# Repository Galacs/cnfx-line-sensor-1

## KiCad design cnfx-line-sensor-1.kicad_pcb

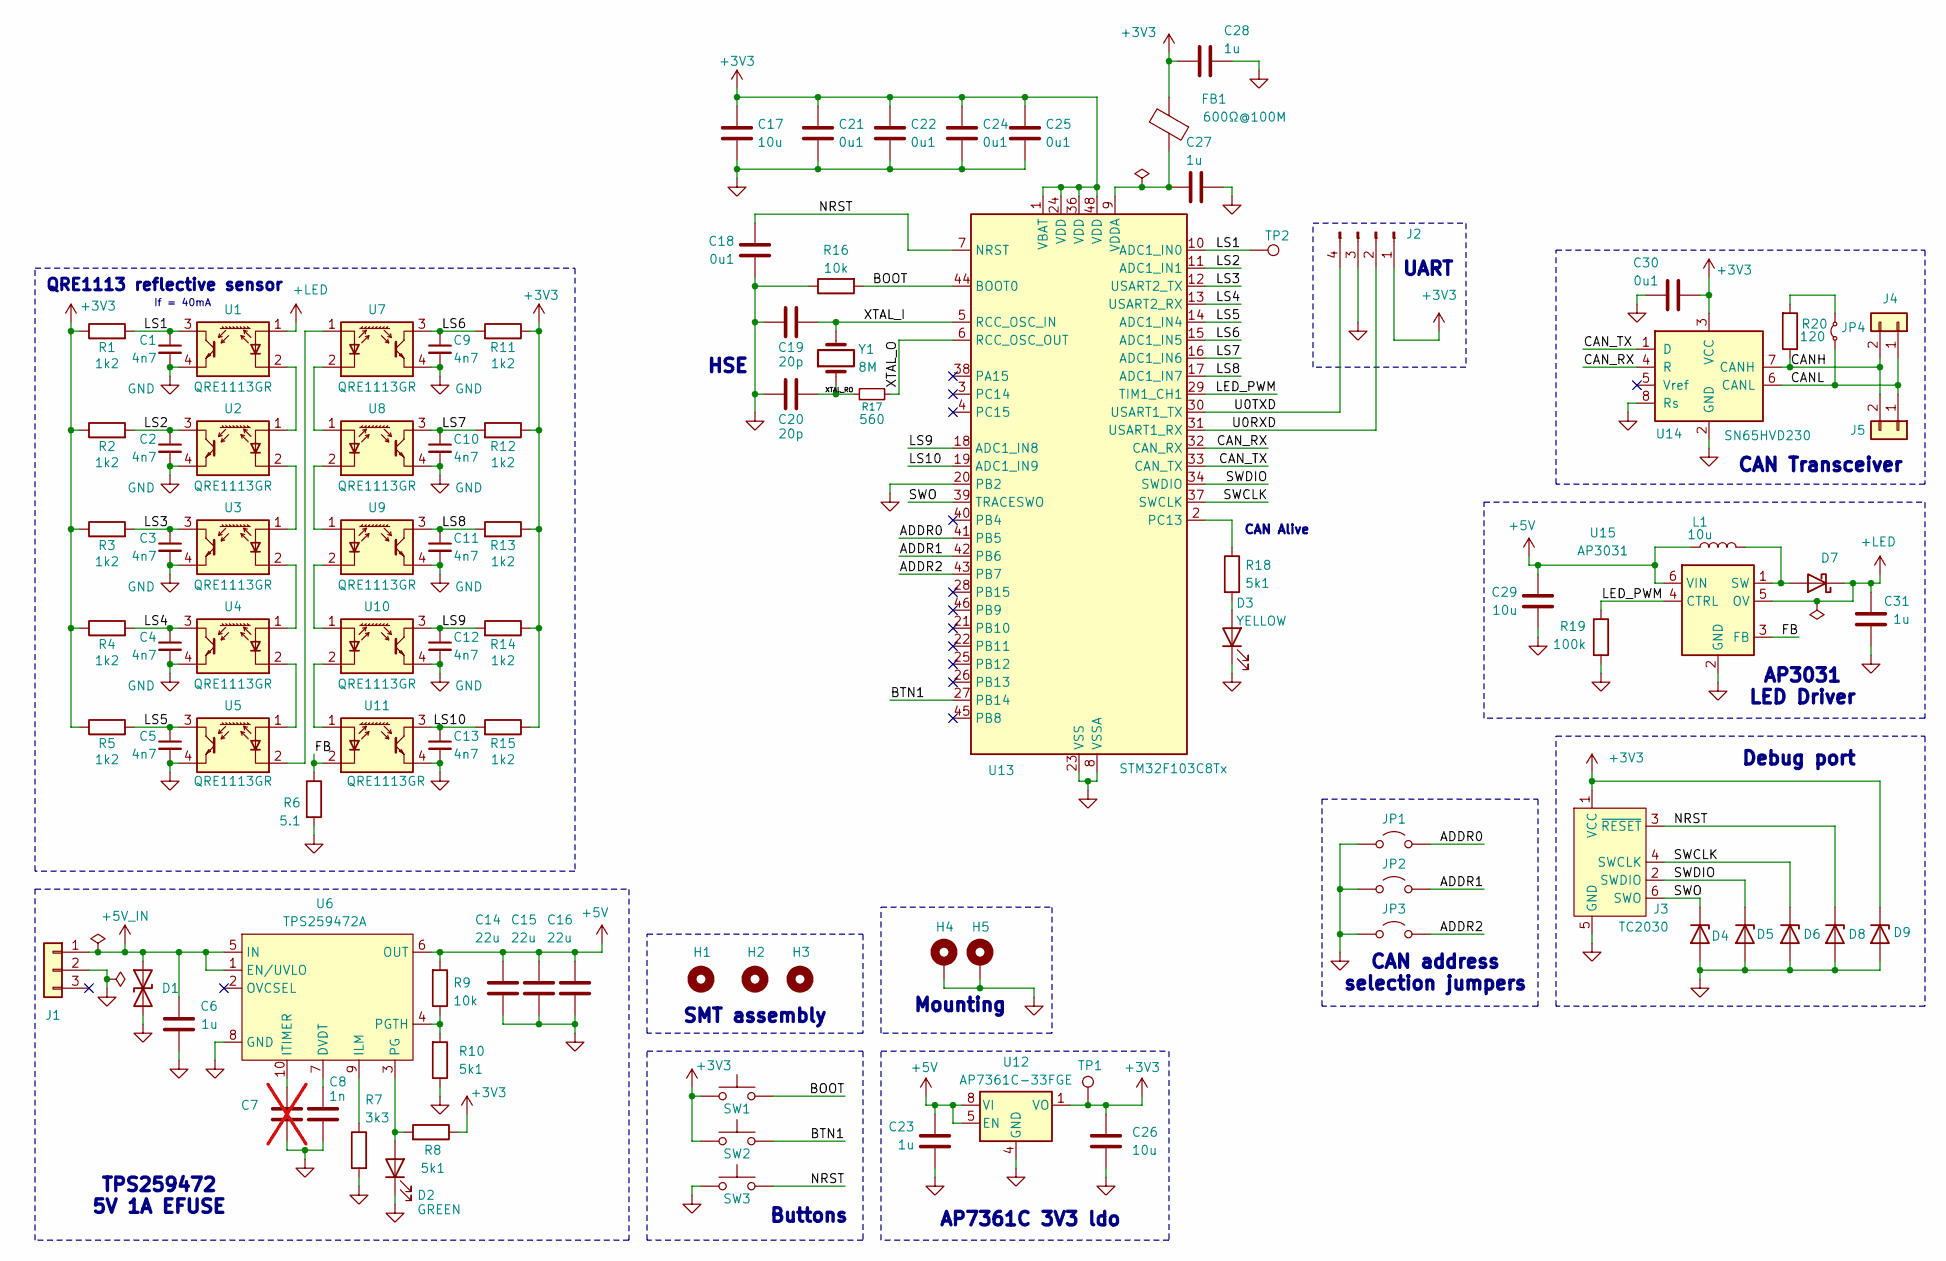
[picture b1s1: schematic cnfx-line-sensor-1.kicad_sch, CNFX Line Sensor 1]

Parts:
C1, C2, C3, C4, C5, C9, C10, C11, C12, C13: 4n7; C_0402_1005Metric; Manufacturer Part Number 0402B472K500NT; JLCPCB Part # C1538
C6, C23, C27, C28, C31: 1u; C_0402_1005Metric; Manufacturer Part Number CL05A105KA5NQNC; JLCPCB Part # C52923
C7: C; C_0402_1005Metric; not fitted
C8: 1n; C_0402_1005Metric; Manufacturer Part Number 0402B102K500NT; JLCPCB Part # C1523
C14, C15, C16: 22u; C_0805_2012Metric; Manufacturer Part Number CL21A226MAQNNNE; JLCPCB Part # C45783
C17, C29: 10u; C_0805_2012Metric; Manufacturer Part Number GRM21BR61H106KE43L; JLCPCB Part # C440198
C18, C21, C22, C24, C25, C30: 0u1; C_0402_1005Metric; Manufacturer Part Number CL05B104KB54PNC; JLCPCB Part # C307331
C19, C20: 20p; C_0603_1608Metric; Manufacturer Part Number CL10C200JB8NNNC; JLCPCB Part # C1648
C26: 10u; C_0402_1005Metric; Manufacturer Part Number CL05A106MQ5NUNC; JLCPCB Part # C15525
D1: SMAJ6.0CA; D_SMA; Manufacturer Part Number SMAJ6.0CA; JLCPCB Part # C19077526
D2: GREEN; LED_0805_2012Metric; Manufacturer Part Number KT-0805G; JLCPCB Part # C2297
D3: YELLOW; LED_0805_2012Metric; Manufacturer Part Number KT-0805Y; JLCPCB Part # C2296
D4, D5, D6, D8, D9: H5VU10U; Diode_DFN1006; Manufacturer Part Number H5VU10U; JLCPCB Part # C22395519
D7: D_Schottky; D_SOD-123; Manufacturer Part Number B5819W SL; JLCPCB Part # C8598
FB1: 600Ω@100M; L_0805_2012Metric; Manufacturer Part Number MPZ2012S601ATD25; JLCPCB Part # C81034
H1, H2, H3: MountingHole; ToolingHole_1.152mm
H4, H5: MountingHole_Pad; MountingHole_3.2mm_M3_Pad_Via
J1: Conn_01x03; JST_XH_B3B-XH-A_1x03_P2.50mm_Vertical; Manufacturer Part Number B3B-XH-A(LF)(SN); JLCPCB Part # C144394
J2: Conn_01x04_Pin; PinHeader_1x04_P2.54mm_Vertical
J3: TC2030; Tag-Connect_TC2030-IDC-NL_2x03_P1.27mm_Vertical
J4, J5: Conn_01x02; JST_XH_B2B-XH-A_1x02_P2.50mm_Vertical; Manufacturer Part Number B2B-XH-A(LF)(SN); JLCPCB Part # C158012
JP1, JP2, JP3: Jumper_2_Open; SolderJumper-2_P1.3mm_Open_RoundedPad1.0x1.5mm
JP4: Jumper_2_Small_Bridged; PinHeader_1x02_P2.54mm_Vertical
L1: 10u; L_Sunlord_MWSA0402S; Manufacturer Part Number TMPC0402HP-100MG-Z02; JLCPCB Part # C305203
R1, R2, R3, R4, R5, R11, R12, R13, R14, R15: 1k2; R_0603_1608Metric; Manufacturer Part Number 0603WAF1201T5E; JLCPCB Part # C22765
R6: 5.1; R_0603_1608Metric; Manufacturer Part Number 0603WAF510KT5E; JLCPCB Part # C25197
R7: 3k3; R_0402_1005Metric; Manufacturer Part Number 0402WGF3301TCE; JLCPCB Part # C25890
R8, R10, R18: 5k1; R_0402_1005Metric; Manufacturer Part Number 0402WGF5101TCE; JLCPCB Part # C25905
R9, R16: 10k; R_0402_1005Metric; Manufacturer Part Number 0402WGF1002TCE; JLCPCB Part # C25744
R17: 560; R_0603_1608Metric; Manufacturer Part Number 0603WAF5600T5E; JLCPCB Part # C23204
R19: 100k; R_0402_1005Metric; Manufacturer Part Number 0402WGF1003TCE; JLCPCB Part # C25741
R20: 120; R_1206_3216Metric; Manufacturer Part Number 1206W4F1200T5E; JLCPCB Part # C17909
SW1, SW2, SW3: SW_Push; SW_SPST_TS-1088-xR020; Manufacturer Part Number TS-1088-AR02016; JLCPCB Part # C720477
TP1, TP2: TestPoint; TestPoint_Pad_D2.0mm
U1, U2, U3, U4, U5, U7, U8, U9, U10, U11: QRE1113GR; OnSemi_CASE100CY; Manufacturer Part Number QRE1113GR; JLCPCB Part # C232862
U6: TPS259472A; Texas_RPW0010A_VQFN-HR-10_2x2mm_P0.5mm; Manufacturer Part Number TPS259472ARPWR; JLCPCB Part # C3662789
U12: AP7361C-33FGE; DFN-8-1EP_3x3mm_P0.65mm_EP1.6x2.56mm_ThermalVias; Manufacturer Part Number AP7361C-33FGE-7; JLCPCB Part # C151007
U13: STM32F103C8Tx; LQFP-48_7x7mm_P0.5mm; Manufacturer Part Number STM32F103C8T6; JLCPCB Part # C8734
U14: SN65HVD230; SOIC-8_3.9x4.9mm_P1.27mm; Manufacturer Part Number SN65HVD230DR; JLCPCB Part # C12084
U15: AP3031; SOT-23-6; Manufacturer Part Number AP3031KTR-G1; JLCPCB Part # C82636
Y1: 8M; Crystal_SMD_5032-2Pin_5.0x3.2mm; Manufacturer Part Number X50328MSB2GI; JLCPCB Part # C115962

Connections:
+3V3: C17.1, C21.1, C22.1, C24.1, C25.1, C26.1, C28.1, C30.1, D9.1 (K), FB1.2, J2.1, J3.1 (VCC), R1.1, R2.1, R3.1, R4.1, R5.1, R8.1, R11.1, R12.1, R13.1, R14.1, R15.1, SW1.1, SW2.1, TP1.1 (1_1), U12.1 (VO), U13.1 (VBAT), U13.24 (VDD), U13.36 (VDD), U13.48 (VDD), U14.3 (VCC)
+5V: C14.1, C15.1, C16.1, C23.1, C29.1, L1.1, R9.2, U6.6 (OUT), U12.5 (EN), U12.8 (VI), U15.6 (VIN)
+5V_IN: C6.2, D1.1 (A1), J1.1, U6.1 (EN/UVLO), U6.5 (IN)
+LED: C31.2, D7.1 (K), U1.1 (A), U15.5 (OV)
/ADDR0: JP1.2 (B), U13.41 (PB5)
/ADDR1: JP2.2 (B), U13.42 (PB6)
/ADDR2: JP3.2 (B), U13.43 (PB7)
/BOOT: R16.2, SW1.2, U13.44 (BOOT0)
/BTN1: SW2.2, U13.27 (PB14)
/CANH: J4.2, J5.2, R20.1, U14.7 (CANH)
/CANL: J4.1, J5.1, JP4.1 (A), U14.6 (CANL)
/CAN_RX: U13.32 (CAN_RX), U14.4 (R)
/CAN_TX: U13.33 (CAN_TX), U14.1 (D)
/FB: R6.1, U11.2 (K), U15.3 (FB)
/LED_PWM: R19.1, U13.29 (TIM1_CH1), U15.4 (CTRL)
/LS1: C1.1, R1.2, TP2.1 (1_1), U1.3, U13.10 (ADC1_IN0)
/LS2: C2.1, R2.2, U2.3, U13.11 (ADC1_IN1)
/LS3: C3.1, R3.2, U3.3, U13.12 (USART2_TX)
/LS4: C4.1, R4.2, U4.3, U13.13 (USART2_RX)
/LS5: C5.1, R5.2, U5.3, U13.14 (ADC1_IN4)
/LS6: C9.1, R11.2, U7.3, U13.15 (ADC1_IN5)
/LS7: C10.1, R12.2, U8.3, U13.16 (ADC1_IN6)
/LS8: C11.1, R13.2, U9.3, U13.17 (ADC1_IN7)
/LS9: C12.1, R14.2, U10.3, U13.18 (ADC1_IN8)
/LS10: C13.1, R15.2, U11.3, U13.19 (ADC1_IN9)
/NRST: C18.1, D8.1 (K), J3.3 (~RESET), SW3.2, U13.7 (NRST)
/SWCLK: D6.1 (K), J3.4 (SWCLK), U13.37 (SWCLK)
/SWDIO: D5.1 (K), J3.2 (SWDIO), U13.34 (SWDIO)
/SWO: D4.1 (K), J3.6 (SWO), U13.39 (TRACESWO)
/U0RXD: J2.2, U13.31 (USART1_RX)
/U0TXD: J2.4, U13.30 (USART1_TX)
/XTAL_I: C19.1, U13.5 (RCC_OSC_IN), Y1.2
/XTAL_O: R17.2, U13.6 (RCC_OSC_OUT)
/XTAL_RO: C20.1, R17.1, Y1.1
GND: C1.2, C2.2, C3.2, C4.2, C5.2, C6.1, C7.2, C8.2, C9.2, C10.2, C11.2, C12.2, C13.2, C14.2, C15.2, C16.2, C17.2, C18.2, C19.2, C20.2, C21.2, C22.2, C23.2, C24.2, C25.2, C26.2, C27.2, C28.2, C29.2, C30.2, C31.1, D1.2 (A2), D2.1 (K), D3.1 (K), D4.2 (A), D5.2 (A), D6.2 (A), D8.2 (A), D9.2 (A), H4.1 (1_1), H5.1 (1_1), J1.2, J2.3, J3.5 (GND), JP1.1 (A), JP2.1 (A), JP3.1 (A), R6.2, R7.2, R10.1, R16.1, R19.2, SW3.1, U1.4, U2.4, U3.4, U4.4, U5.4, U6.8 (GND), U7.4, U8.4, U9.4, U10.4, U11.4, U12.4 (GND), U12.9 (GND), U13.8 (VSSA), U13.20 (PB2), U13.23 (VSS), U13.35 (VSS), U13.47 (VSS), U14.2 (GND), U14.8 (Rs), U15.2 (GND)
unnamed: D2.2 (A), R8.2, U6.3 (PG)
unnamed: D3.2 (A), R18.2
unnamed: D7.2 (A), L1.2, U15.1 (SW)
unnamed: JP4.2 (B), R20.2
unnamed: U1.2 (K), U2.1 (A)
unnamed: U2.2 (K), U3.1 (A)
unnamed: U3.2 (K), U4.1 (A)
unnamed: U4.2 (K), U5.1 (A)
unnamed: U5.2 (K), U7.1 (A)
unnamed: C8.1, U6.7 (DVDT)
unnamed: R7.1, U6.9 (ILM)
unnamed: C7.1, U6.10 (ITIMER)
unnamed: R9.1, R10.2, U6.4 (PGTH)
unnamed: U7.2 (K), U8.1 (A)
unnamed: U8.2 (K), U9.1 (A)
unnamed: U9.2 (K), U10.1 (A)
unnamed: U10.2 (K), U11.1 (A)
unnamed: R18.1, U13.2 (PC13)
unnamed: C27.1, FB1.1, U13.9 (VDDA)

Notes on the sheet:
SMT assembly
If = 40mA
CAN Alive
QRE1113 reflective sensor
HSE
AP7361C 3V3 ldo
Debug port
TPS259472 5V 1A EFUSE
UART
CAN Transceiver
AP3031 LED Driver
Buttons
CAN address selection jumpers
Mounting

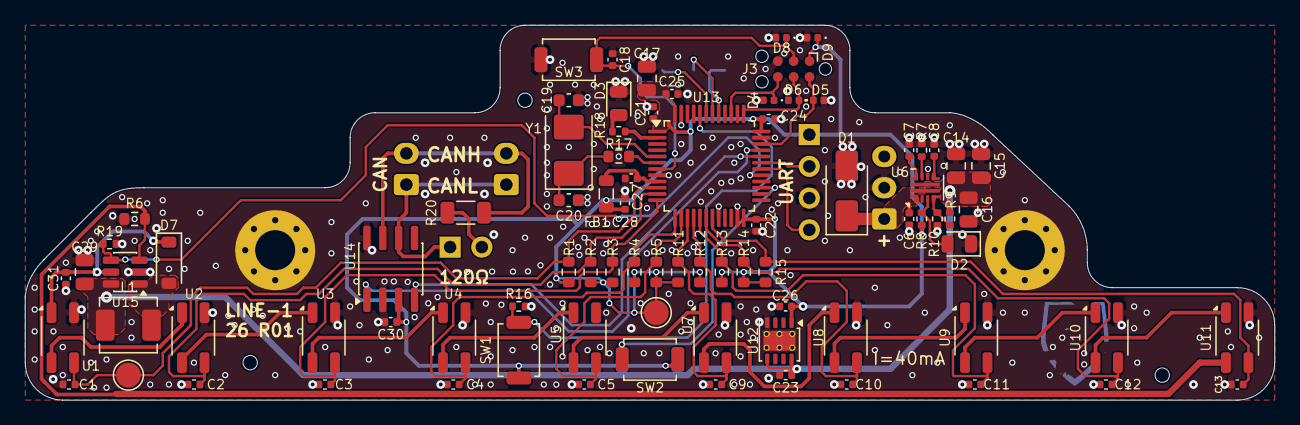
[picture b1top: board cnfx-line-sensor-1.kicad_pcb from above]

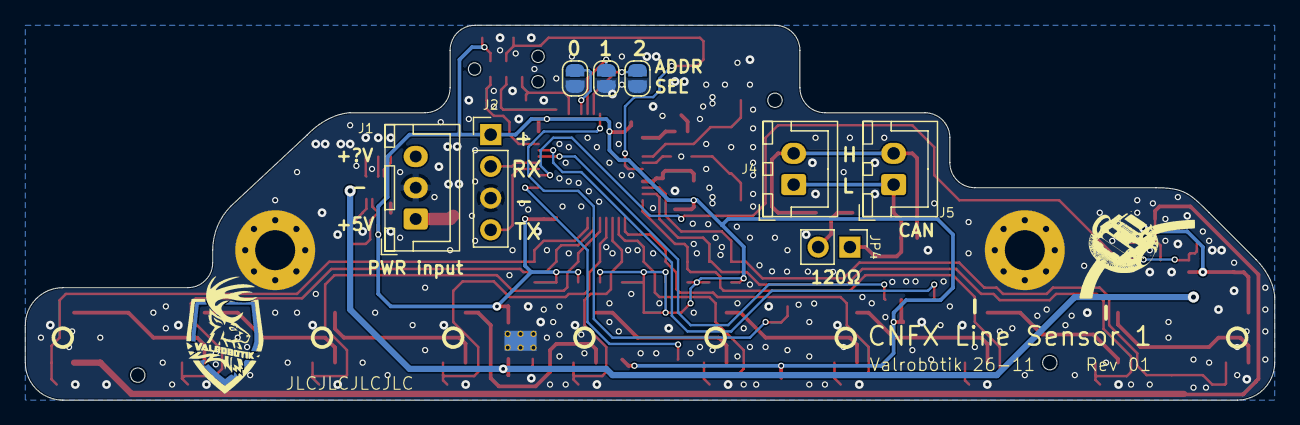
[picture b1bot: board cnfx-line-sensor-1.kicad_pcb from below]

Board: 2 copper layers, 100.0 x 30.0 mm, 97 parts (8 on the bottom side), 54 nets.

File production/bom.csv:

Designator,Footprint,Quantity,Value,LCSC Part #
"C1, C10, C11, C12, C13, C2, C3, C4, C5, C9",0402,10,4n7,C1538
"C14, C15, C16",0805,3,22u,C45783
"C17, C29",0805,2,10u,C440198
"C18, C21, C22, C24, C25, C30",0402,6,0u1,C307331
"C19, C20",0603,2,20p,C1648
"C23, C27, C28, C31, C6",0402,5,1u,C52923
C26,0402,1,10u,C15525
C8,0402,1,1n,C1523
D1,D_SMA,1,SMAJ6.0CA,C19077526
D2,0805,1,GREEN,C2297
D3,0805,1,YELLOW,C2296
"D4, D5, D6, D8, D9",Diode_DFN1006,5,H5VU10U,C22395519
D7,D_SOD-123,1,D_Schottky,C8598
FB1,0805,1,600Ω@100M,C81034
J1,JST_XH_B3B-XH-A_1x03_P2.50mm_Vertical,1,Conn_01x03,C144394
"J4, J5",JST_XH_B2B-XH-A_1x02_P2.50mm_Vertical,2,Conn_01x02,C158012
L1,L_Sunlord_MWSA0402S,1,10u,C305203
"R1, R11, R12, R13, R14, R15, R2, R3, R4, R5",0603,10,1k2,C22765
"R10, R18, R8",0402,3,5k1,C25905
"R16, R9",0402,2,10k,C25744
R17,0603,1,560,C23204
R19,0402,1,100k,C25741
R20,1206,1,120,C17909
R6,0603,1,5.1,C25197
R7,0402,1,3k3,C25890
"SW1, SW2, SW3",SW_SPST_TS-1088-xR020,3,SW_Push,C720477
"U1, U10, U11, U2, U3, U4, U5, U7, U8, U9",OnSemi_CASE100CY,10,QRE1113GR,C232862
U12,DFN-8-1EP_3x3mm_P0.65mm_EP1.6x2.56mm_ThermalVias,1,AP7361C-33FGE,C151007
U13,LQFP-48_7x7mm_P0.5mm,1,STM32F103C8Tx,C8734
U14,SOIC-8_3.9x4.9mm_P1.27mm,1,SN65HVD230,C12084
U15,SOT-23-6,1,AP3031,C82636
U6,Texas_RPW0010A_VQFN-HR-10_2x2mm_P0.5mm,1,TPS259472A,C3662789
Y1,Crystal_SMD_5032-2Pin_5.0x3.2mm,1,8M,C115962
